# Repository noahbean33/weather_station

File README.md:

FPGA-Accelerated Digital Radio Receiver
A proof-of-concept digital radio that uses a Xilinx Artix-7 FPGA for real-time DSP and an ESP32 microcontroller for system control. The project demonstrates core competencies in FPGA design, embedded C, and RF system integration using off-the-shelf hardware modules.

This project is intentionally scoped for rapid development and focuses on creating a demonstrable system that showcases key engineering skills for a resume or portfolio.

Core Features
FPGA DSP: Real-time mono FM demodulation implemented in SystemVerilog.

MCU Control: An ESP32 running C (ESP-IDF) controls the radio tuner and user interface.

User Interface: A rotary encoder for tuning and an OLED screen to display the current frequency.

System Integration: All components are integrated on a breadboard or protoboard for straightforward assembly and debugging.

🛠️ Hardware Components
FPGA Board: Digilent Nexys A7 (or similar Artix-7 board).

Microcontroller: ESP32 Development Board (e.g., ESP32-DevKitC).

RF Tuner: Si4703 Breakout Board. This module simplifies the RF stage by handling tuning and providing a standard I2S digital audio output.

Display: I2C OLED Display (e.g., SSD1306 128x64).

Audio Output: I2S Amplifier Breakout Board (e.g., MAX98357A). This accepts the digital audio stream directly from the FPGA.

Input Control: One rotary encoder for tuning.

Power Supply: USB power or a benchtop power supply.

🏗️ System Architecture
Code snippet

graph TD
    A[Antenna] --> RF_TUNER;
    RF_TUNER[Si4703 Tuner Breakout];
    UI_Knob[Tuning Knob] --> ESP32;
    ESP32[ESP32 Dev Board (C Firmware)];
    ESP32 -- I2C --> RF_TUNER;
    ESP32 -- I2C --> OLED[OLED Display];

    subgraph "FPGA DSP (Artix-7)"
        ARTIX7[Xilinx Artix-7 FPGA]
        I2S_IN[I2S Input]
        FM_DEMOD[Mono FM Demodulator]
        I2S_OUT[I2S Output]

        I2S_IN --> FM_DEMOD;
        FM_DEMOD --> I2S_OUT;
    end

    RF_TUNER -- Digital Audio (I2S) --> I2S_IN;
    I2S_OUT --> DAC_AMP[I2S DAC/Amplifier];
    DAC_AMP --> Speaker;
System Flow:

The ESP32 instructs the Si4703 Tuner via I2C to tune to a specific frequency.

The tuner receives the radio signal and outputs a digital I2S audio stream.

The Artix-7 FPGA receives the I2S stream, performs mono FM demodulation in real-time, and outputs a processed I2S stream.

An I2S Amplifier receives the clean digital audio from the FPGA, converts it to analog, and drives a speaker.

The ESP32 displays the current frequency on the OLED screen.

💻 Software & Tools
FPGA Development:

Language: SystemVerilog

Toolchain: Xilinx Vivado Design Suite

Simulation: Vivado Simulator (XSIM)

Embedded Firmware (ESP32):

Language: C / C++

Framework: ESP-IDF (Espressif IoT Development Framework)

Tools: idf.py command-line tool

🚀 Project Plan
Phase 1: Core Controller Setup

[ ] Set up the ESP-IDF environment.

[ ] Interface the ESP32 with the OLED display and rotary encoder.

[ ] Write firmware to control the Si4703 tuner via I2C and display the frequency.

Milestone: Tune to an FM station and listen to the raw (undemodulated) output if possible, proving tuner control.

Phase 2: FPGA DSP Implementation

[ ] Set up the Xilinx Vivado environment.

[ ] Design and simulate a mono FM demodulator in SystemVerilog.

[ ] Implement I2S input and output interfaces on the FPGA.

[ ] Synthesize the design and program the Nexys A7 board.

Milestone: Pass a test I2S signal through the FPGA without modification (pass-through test).

Phase 3: System Integration & Testing

[ ] Connect all hardware modules on a breadboard.

[ ] Route the I2S signal from the tuner, through the FPGA, to the I2S amplifier.

[ ] Debug the complete system to achieve clear audio output.

Milestone: A fully functional radio that tunes via the knob and plays audio processed by the FPGA.

📁 Repository Structure
.
├── firmware/esp32             # ESP32 ESP-IDF C/C++ firmware
│   ├── main/
│   │   └── main.c
│   ├── components/
│   └── CMakeLists.txt
├── fpga/artix7                # Xilinx Artix-7 SystemVerilog code
│   ├── src/                   # Source files (.sv)
│   ├── sim/                   # Simulation files and testbenches
│   └── constraints/           # Pin and timing constraints (.xdc)
├── docs/                      # Documentation, diagrams, images
└── README.md
⚡ How to Build & Use
Firmware (ESP32)
Install the ESP-IDF toolchain from Espressif.

Navigate to firmware/esp32.

Build: idf.py build

Flash & Monitor: idf.py -p /dev/ttyUSB0 flash monitor (adjust port as needed).

FPGA (Artix-7)
Install the Xilinx Vivado Design Suite.

Open the Vivado project from the fpga/artix7 directory.

Run Synthesis, Implementation, and Generate Bitstream.

Program the FPGA using the Vivado Hardware Manager.

Acknowledgements
Digilent for the Nexys A7 board and support.

Espressif Systems for the ESP32 and the ESP-IDF.

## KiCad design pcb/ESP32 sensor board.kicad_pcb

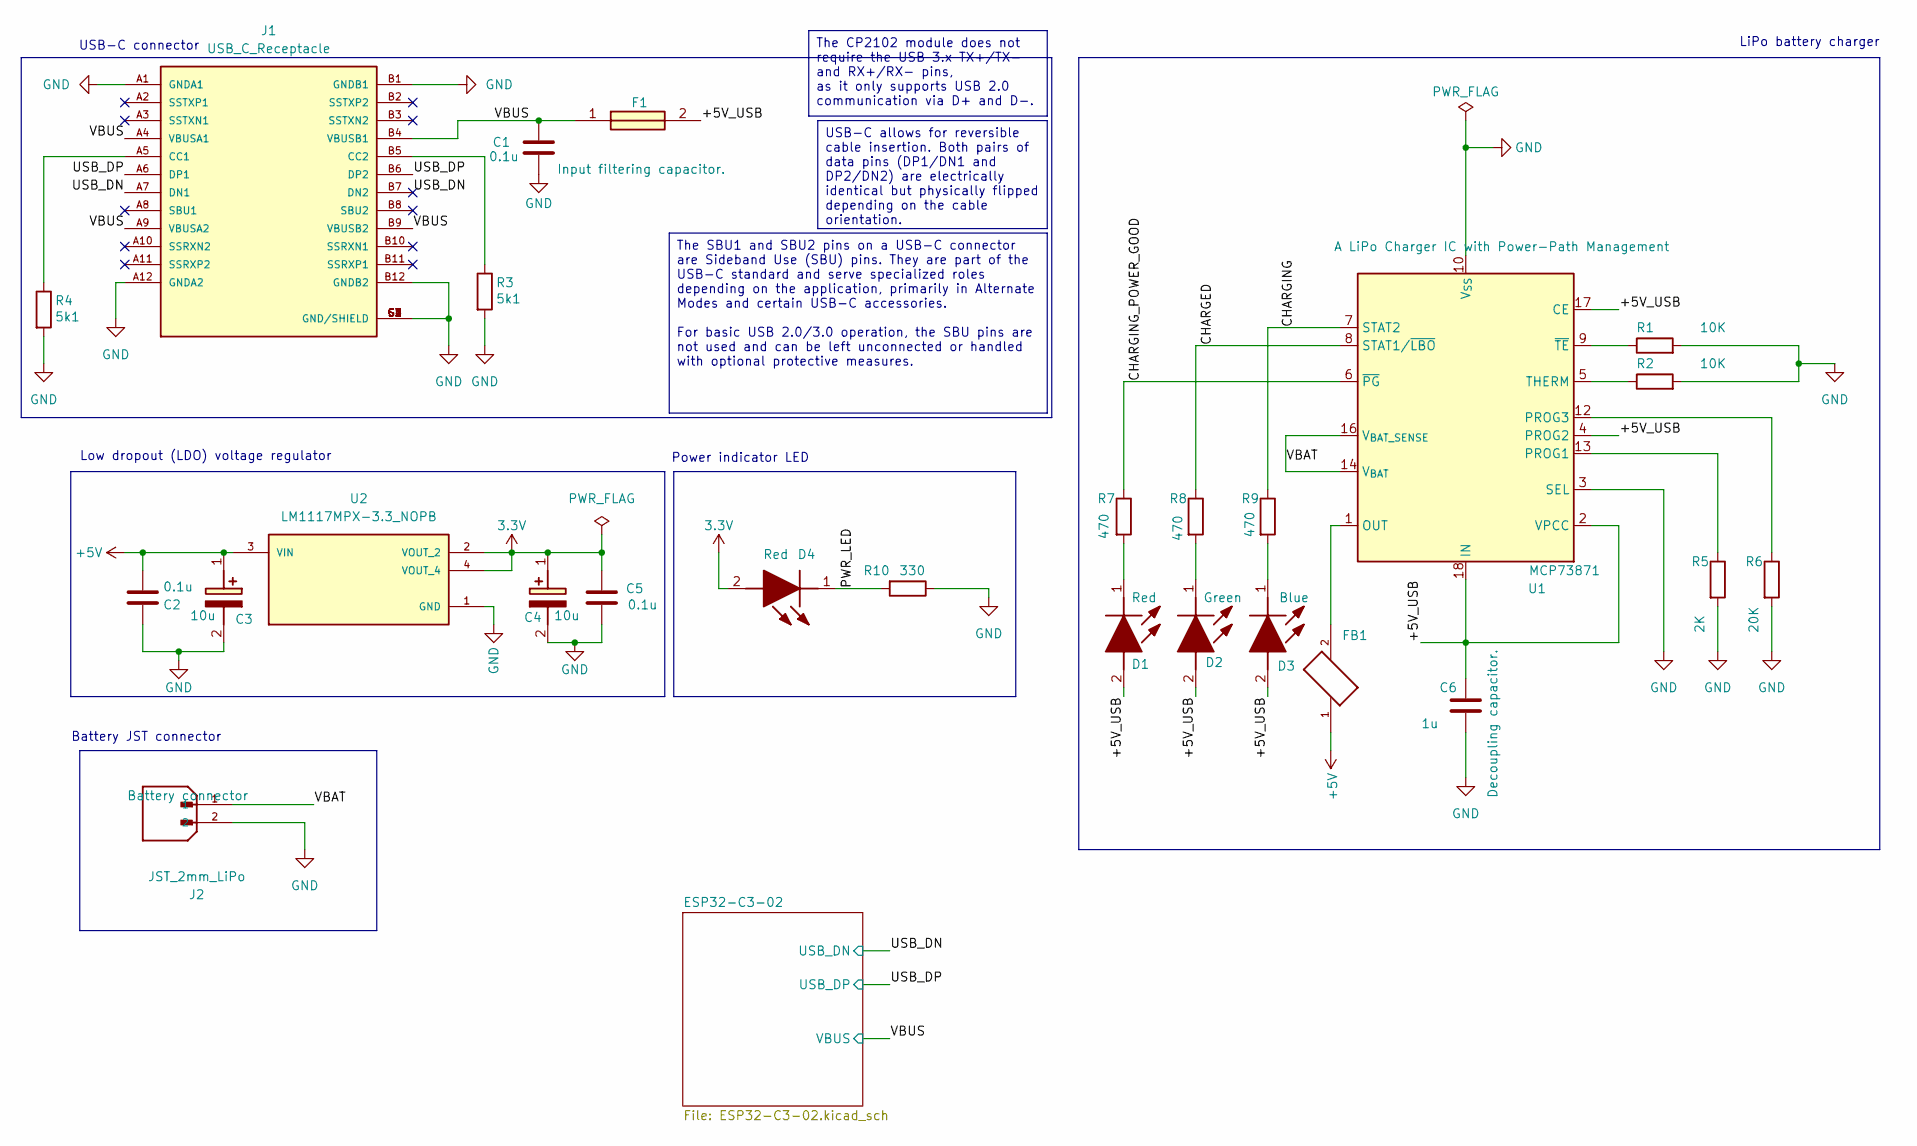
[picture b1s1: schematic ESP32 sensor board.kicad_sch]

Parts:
C1, C2, C5: 0.1u; C_0805_2012Metric; Voltage 1kV; Tolerance 100%
C3, C4: 10u; T491A; Voltage 1kV; Tolerance 100%; Manufacturer_Part_Number T491A106K010AT7280; Mouser Part Number 80-T491A106K107280
C6: 1u; C_0805_2012Metric; Voltage 1kV; Tolerance 100%
D1, D4: Red; LEDC2012X120N; Manufacturer_Part_Number LTST-C170KRKT; Mouser Part Number 859-LTST-C170KRKT
D2: Green; LEDC2012X120N; Manufacturer_Part_Number LTST-C170GKT; Mouser Part Number 859-LTST-C170GKT
D3: Blue; LEDC2012X120N; Manufacturer_Part_Number LTST-C170TBKT; Mouser Part Number 859-LTST-C170TBKT
F1: 0ZCH0110AF2E; FUSC3226X100N; Manufacturer_Part_Number 0ZCH0110AF2E
FB1: FBMJ2125HM330-T; BEADC2012X105N
J1: USB_C_Receptacle; BELFUSE_SS-52400-002; PARTREV A0
J2: JST_2mm_LiPo; JST_B2B-PH-SM4-TB; Manufacturer_Part_Number ?
R1, R2: 10K; R_0805_2012Metric
R3, R4: 5k1; R_0805_2012Metric
R5: 2K; R_0805_2012Metric
R6: 20K; R_0805_2012Metric
R7, R8, R9: 470; R_0805_2012Metric
R10: 330; R_0805_2012Metric
U1: MCP73871; QFN-20-1EP_4x4mm_P0.5mm_EP2.5x2.5mm; Manufacturer_Part_Number MCP73871-4CCI/ML
U2: LM1117MPX-3.3_NOPB; VREG_LM1117MPX-3.3; Mouser Part Number 926-LM1117MPX3.3NOPB

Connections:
3.3V: C4.1 (+), C5.1, D4.2 (A), U2.2 (VOUT_2), U2.4 (VOUT_4); also elsewhere on the board
+5V: C2.1, C3.1 (+), FB1.1, U2.3 (VIN)
/+5V_USB: C6.1, D1.2 (A), D2.2 (A), D3.2 (A), F1.2, U1.2 (VPCC), U1.4 (PROG2), U1.17 (CE), U1.18 (IN), U1.19 (IN)
/CHARGED: R8.1, U1.8 (STAT1/~LBO)
/CHARGING: R9.1, U1.7 (STAT2)
/CHARGING_POWER_GOOD: R7.1, U1.6 (~PG)
/PWR_LED: D4.1 (K), R10.2
/USB_DN: J1.A7 (DN1), J1.B7 (DN2); also elsewhere on the board
/USB_DP: J1.A6 (DP1), J1.B6 (DP2); also elsewhere on the board
/VBAT: J2.1, U1.14 (V_{BAT}), U1.15 (V_{BAT}), U1.16 (V_{BAT_SENSE})
/VBUS: C1.1, F1.1, J1.A4 (VBUSA1), J1.A9 (VBUSA2), J1.B4 (VBUSB1), J1.B9 (VBUSB2); also elsewhere on the board
GND: C1.2, C2.2, C3.2 (-), C4.2 (-), C5.2, C6.2, J1.A1 (GNDA1), J1.A12 (GNDA2), J1.B1 (GNDB1), J1.B12 (GNDB2), J1.G1 (GND/SHIELD), J1.G2 (GND/SHIELD), J1.G3 (GND/SHIELD), J1.G4 (GND/SHIELD), J1.S1 (GND/SHIELD), J1.S2 (GND/SHIELD), J1.S3 (GND/SHIELD), J1.S4 (GND/SHIELD), J2.2, R1.2, R2.2, R3.2, R4.2, R5.2, R6.2, R10.1, U1.3 (SEL), U1.10 (V_{SS}), U1.11 (V_{SS}), U1.21 (V_{SS}), U2.1 (GND); also elsewhere on the board
unnamed: D1.1 (K), R7.2
unnamed: D2.1 (K), R8.2
unnamed: D3.1 (K), R9.2
unnamed: FB1.2, U1.1 (OUT), U1.20 (OUT)
unnamed: J1.A5 (CC1), R4.1
unnamed: J1.B5 (CC2), R3.1
unnamed: R5.1, U1.13 (PROG1)
unnamed: R6.1, U1.12 (PROG3)
unnamed: R2.1, U1.5 (THERM)
unnamed: R1.1, U1.9 (~TE)

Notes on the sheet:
USB-C connector
LiPo battery charger
Power indicator LED
Low dropout (LDO) voltage regulator
Battery JST connector
The CP2102 module does not require the USB 3.x TX+/TX- and RX+/RX- pins, as it only supports USB 2.0 communication via D+ and D-.
The SBU1 and SBU2 pins on a USB-C connector are Sideband Use (SBU) pins. They are part of the USB-C standard and serve specialized roles depending on the application, primarily in Alternate Modes and certain USB-C accessories. For basic USB 2.0/3.0 operation, the SBU pins are not used and can be le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
USB-C allows for reversible cable insertion. Both pairs of data pins (DP1/DN1 and DP2/DN2) are electrically identical but physically flipped depending on the cable orientation.

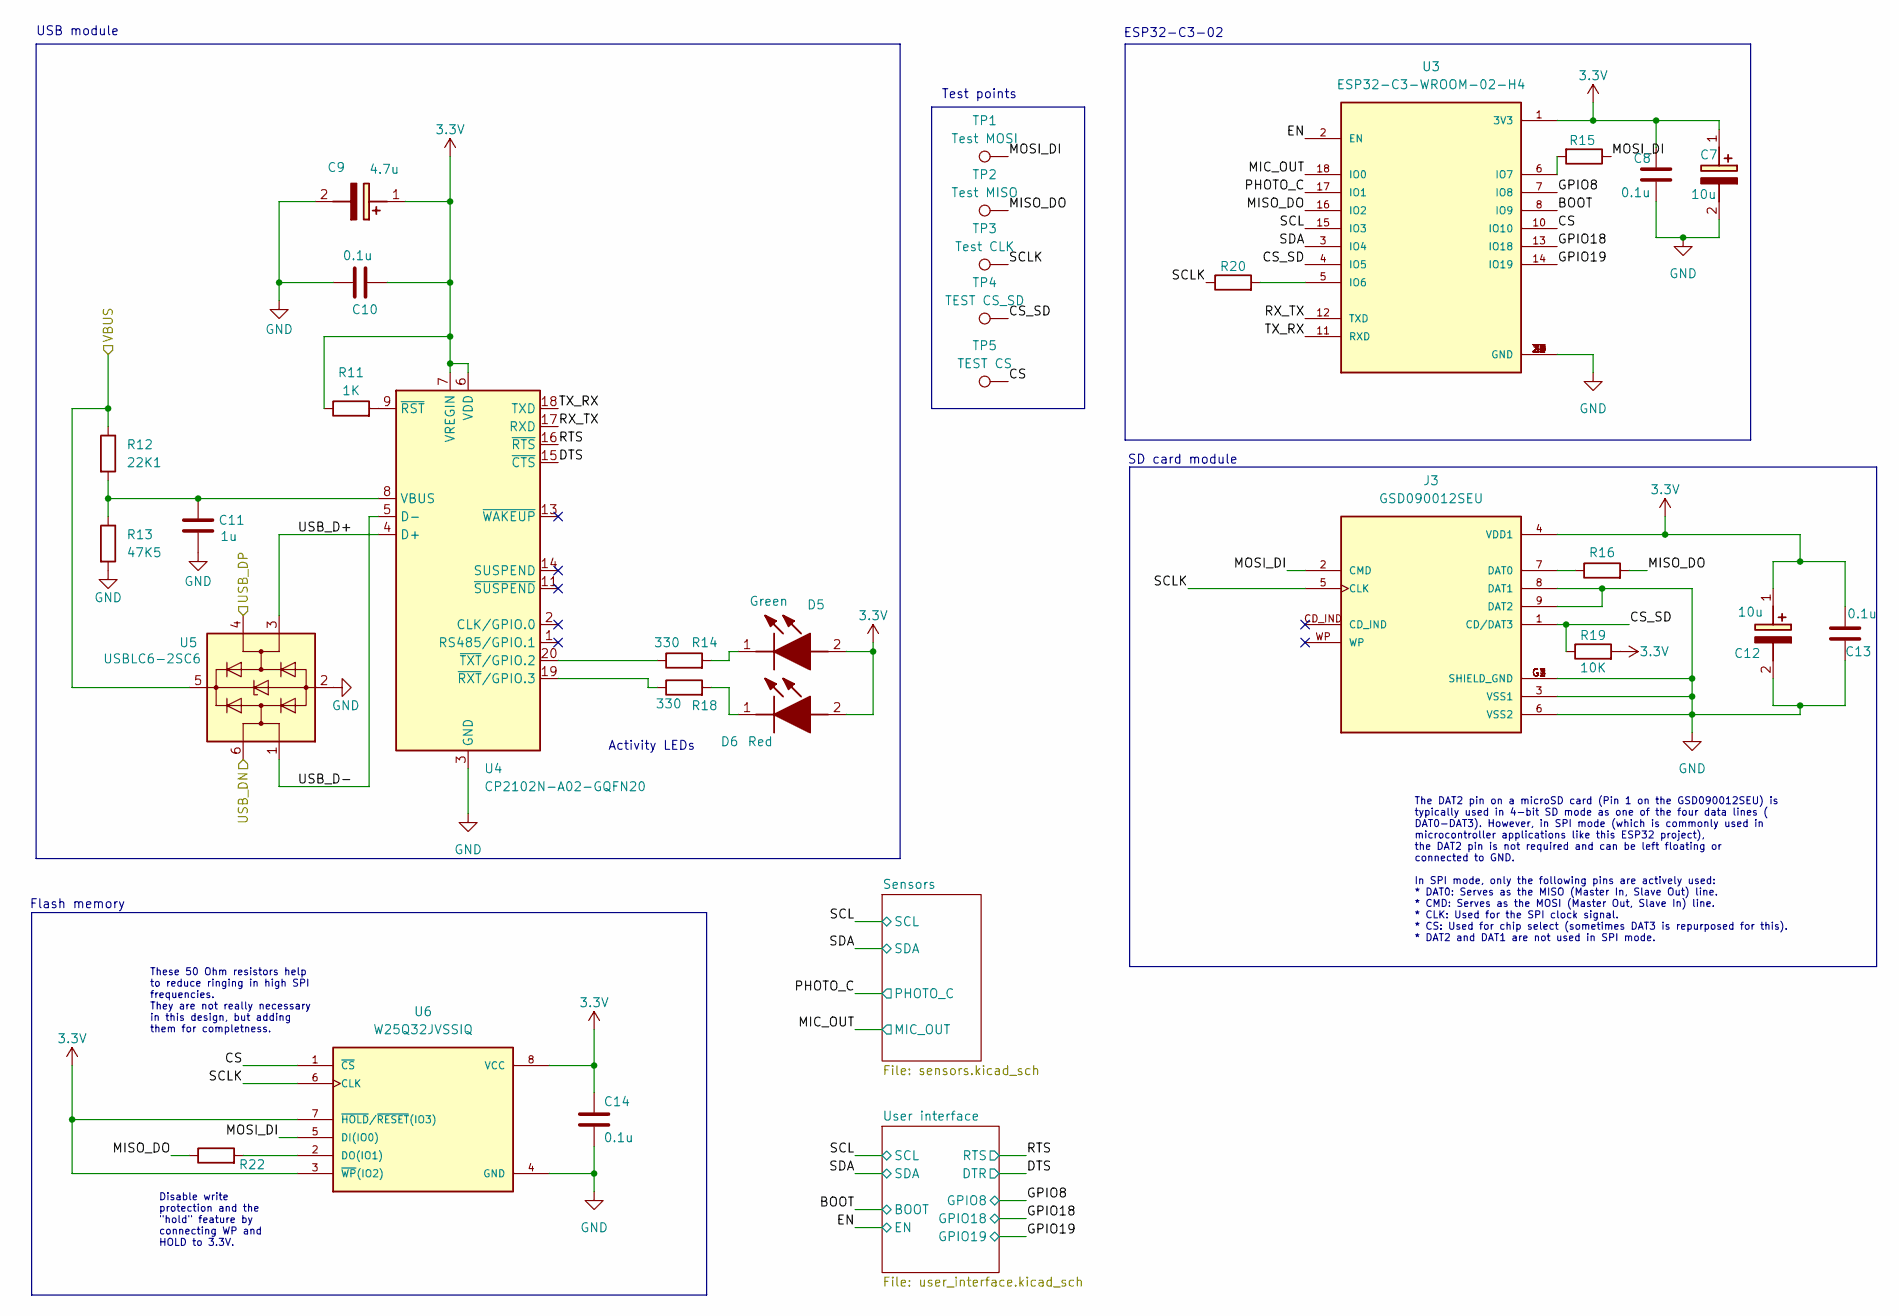
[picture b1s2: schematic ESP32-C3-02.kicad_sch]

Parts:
C7, C12: 10u; T491A; Voltage 1kV; Tolerance 100%; Manufacturer_Part_Number T491A106K010AT7280; Mouser Part Number 80-T491A106K107280
C8, C10, C13, C14: 0.1u; C_0805_2012Metric; Voltage 1kV; Tolerance 100%
C9: 4.7u; T491A; Voltage 1kV; Tolerance 100%; Manufacturer_Part_Number T491A106K010AT7280; Mouser Part Number 80-T491A106K107280
C11: 1u; C_0805_2012Metric; Voltage 1kV; Tolerance 100%
D5: Green; LEDC2012X120N; Manufacturer_Part_Number LTST-C170GKT; Mouser Part Number 859-LTST-C170GKT
D6: Red; LEDC2012X120N; Manufacturer_Part_Number LTST-C170KRKT; Mouser Part Number 859-LTST-C170KRKT
J3: GSD090012SEU; AMPHENOL_GSD090012SEU; PARTREV E
R11: 1K; R_0805_2012Metric
R12: 22K1; R_0805_2012Metric
R13: 47K5; R_0805_2012Metric
R14, R18: 330; R_0805_2012Metric
R15, R16, R20, R22: 50; R_0805_2012Metric
R19: 10K; R_0805_2012Metric
TP1: Test MOSI; TestPoint_Pad_D1.0mm
TP2: Test MISO; TestPoint_Pad_D1.0mm
TP3: Test CLK; TestPoint_Pad_D1.0mm
TP4: TEST CS_SD; TestPoint_Pad_D1.0mm
TP5: TEST CS; TestPoint_Pad_D1.0mm
U3: ESP32-C3-WROOM-02-H4; MODULE_ESP32-C3-WROOM-02-H4; Manufacturer_Part_Number ESP32-C3-WROOM-02-H4
U4: CP2102N-A02-GQFN20; SiliconLabs_QFN-20-1EP_3x3mm_P0.5mm_EP1.8x1.8mm; Manufacturer_Part_Number CP2102N-A02-GQFN20
U5: USBLC6-2SC6; SOT-23-6; Manufacturer_Part_Number USBLC6-2SC6; Mouser Part Number 511-USBLC6-2SC6
U6: W25Q32JVSSIQ; SOIC127P790X216-8N; M_PART_NUMBER W25QXX

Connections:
3.3V: C7.1 (+), C8.1, C9.1 (+), C10.1, C12.1 (+), C13.2, C14.1, D5.2 (A), D6.2 (A), J3.4 (VDD1), R11.1, R19.2, U3.1 (3V3), U4.6 (VDD), U4.7 (VREGIN), U6.3 (~WP(IO2)), U6.7 (~HOLD/~RESET(IO3)), U6.8 (VCC); also elsewhere on the board
/ESP32-C3-02/BOOT: U3.8 (IO9); also elsewhere on the board
/ESP32-C3-02/CS: TP5.1 (1_1), U3.10 (IO10), U6.1 (~CS)
/ESP32-C3-02/CS_SD: J3.1 (CD/DAT3), R19.1, TP4.1 (1_1), U3.4 (IO5)
/ESP32-C3-02/DTS: U4.15 (~CTS); also elsewhere on the board
/ESP32-C3-02/EN: U3.2 (EN); also elsewhere on the board
/ESP32-C3-02/GPIO8: U3.7 (IO8); also elsewhere on the board
/ESP32-C3-02/GPIO18: U3.13 (IO18); also elsewhere on the board
/ESP32-C3-02/GPIO19: U3.14 (IO19); also elsewhere on the board
/ESP32-C3-02/MIC_OUT: U3.18 (IO0); also elsewhere on the board
/ESP32-C3-02/MISO_DO: R16.2, R22.1, TP2.1 (1_1), U3.16 (IO2)
/ESP32-C3-02/MOSI_DI: J3.2 (CMD), R15.1, TP1.1 (1_1), U6.5 (DI(IO0))
/ESP32-C3-02/PHOTO_C: U3.17 (IO1); also elsewhere on the board
/ESP32-C3-02/RTS: U4.16 (~RTS); also elsewhere on the board
/ESP32-C3-02/RX_TX: U3.12 (TXD), U4.17 (RXD)
/ESP32-C3-02/SCL: U3.15 (IO3); also elsewhere on the board
/ESP32-C3-02/SCLK: J3.5 (CLK), R20.1, TP3.1 (1_1), U6.6 (CLK)
/ESP32-C3-02/SDA: U3.3 (IO4); also elsewhere on the board
/ESP32-C3-02/TX_RX: U3.11 (RXD), U4.18 (TXD)
/ESP32-C3-02/USB_D+: U4.4 (D+), U5.3 (I/O2)
/ESP32-C3-02/USB_D-: U4.5 (D-), U5.1 (I/O1)
/USB_DN: U5.6 (I/O1); also elsewhere on the board
/USB_DP: U5.4 (I/O2); also elsewhere on the board
/VBUS: R12.1, U5.5 (VBUS); also elsewhere on the board
GND: C7.2 (-), C8.2, C9.2 (-), C10.2, C11.2, C12.2 (-), C13.1, C14.2, J3.3 (VSS1), J3.6 (VSS2), J3.8 (DAT1), J3.9 (DAT2), J3.G1 (SHIELD_GND), J3.G2 (SHIELD_GND), J3.G3 (SHIELD_GND), J3.G4 (SHIELD_GND), R13.2, U3.9 (GND), U3.19 (GND), U3.20 (GND), U3.21 (GND), U3.22 (GND), U3.23 (GND), U3.24 (GND), U3.25 (GND), U3.26 (GND), U3.27 (GND), U3.28 (GND), U3.29 (GND), U3.30 (GND), U3.31 (GND), U3.32 (GND), U3.33 (GND), U3.34 (GND), U3.35 (GND), U3.36 (GND), U3.37 (GND), U3.38 (GND), U3.39 (GND), U4.3 (GND), U4.12 (GND), U4.21 (GND), U5.2 (GND), U6.4 (GND); also elsewhere on the board
unnamed: D5.1 (K), R14.2
unnamed: D6.1 (K), R18.2
unnamed: J3.7 (DAT0), R16.1
unnamed: R20.2, U3.5 (IO6)
unnamed: R15.2, U3.6 (IO7)
unnamed: C11.1, R12.2, R13.1, U4.8 (VBUS)
unnamed: R11.2, U4.9 (~RST)
unnamed: R18.1, U4.19 (~RXT/GPIO.3)
unnamed: R14.1, U4.20 (~TXT/GPIO.2)
unnamed: R22.2, U6.2 (DO(IO1))

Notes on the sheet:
SD card module
Activity LEDs
Flash memory
USB module
Test points
ESP32-C3-02
Disable write protection and the "hold" feature by connecting WP and HOLD to 3.3V.
The DAT2 pin on a microSD card (Pin 1 on the GSD090012SEU) is typically used in 4-bit SD mode as one of the four data lines ( DAT0-DAT3). However, in SPI mode (which is commonly used in microcontroller applications like this ESP32 project), the DAT2 pin is not required and can be left floating or c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
These 50 Ohm resistors help to reduce ringing in high SPI frequencies. They are not really necessary in this design, but adding them for completness.

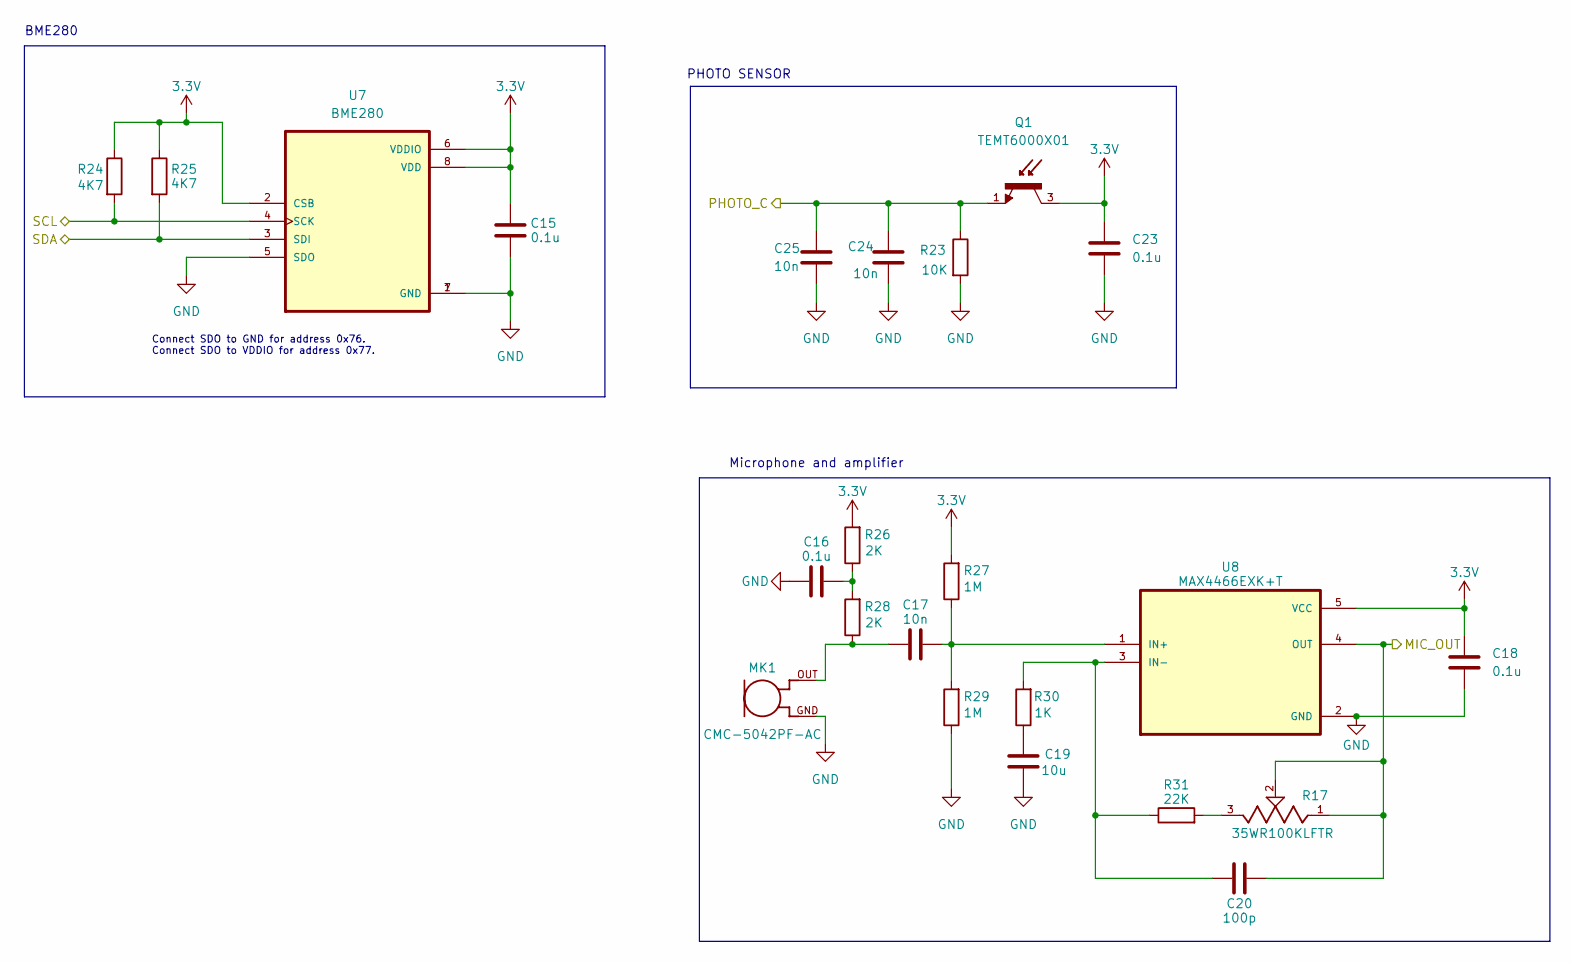
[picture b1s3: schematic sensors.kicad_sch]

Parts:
C15: 0.1u; C_0805_2012Metric; Voltage 1kV; Tolerance 100%
C16, C18, C23: 0.1u; C_0805_2012Metric
C17, C24, C25: 10n; C_0805_2012Metric
C19: 10u; C_0805_2012Metric
C20: 100p; C_0805_2012Metric
MK1: CMC-5042PF-AC; CUI_CMC-5042PF-AC; Manufacturer_Part_Number CMC-5042PF-AC
Q1: TEMT6000X01; TRANS_TEMT6000X01; PARTREV 1.9
R17: 35WR100KLFTR; TRIM_35WR100KLFTR; PARTREV D
R23: 10K; R_0805_2012Metric
R24, R25: 4K7; R_0805_2012Metric
R26, R28: 2K; R_0805_2012Metric
R27, R29: 1M; R_0805_2012Metric
R30: 1K; R_0805_2012Metric
R31: 22K; R_0805_2012Metric
U7: BME280; PSON65P250X250X100-8N; Manufacturer_Part_Number BME280
U8: MAX4466EXK+T; SOT65P210X110-5N; Manufacturer_Part_Number MAX4466EXK+T

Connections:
3.3V: C15.2, C18.1, C23.1, Q1.3, R24.1, R25.1, R26.2, R27.2, U7.2 (CSB), U7.6 (VDDIO), U7.8 (VDD), U8.5 (VCC); also elsewhere on the board
/ESP32-C3-02/MIC_OUT: C20.2, R17.1, R17.2, U8.4 (OUT); also elsewhere on the board
/ESP32-C3-02/PHOTO_C: C24.1, C25.1, Q1.1, R23.1; also elsewhere on the board
/ESP32-C3-02/SCL: R24.2, U7.4 (SCK); also elsewhere on the board
/ESP32-C3-02/SDA: R25.2, U7.3 (SDI); also elsewhere on the board
GND: C15.1, C16.2, C18.2, C19.1, C23.2, C24.2, C25.2, MK1.GND, R23.2, R29.1, U7.1 (GND), U7.5 (SDO), U7.7 (GND), U8.2 (GND); also elsewhere on the board
unnamed: C16.1, R26.1, R28.2
unnamed: C17.2, MK1.OUT, R28.1
unnamed: C19.2, R30.1
unnamed: R17.3, R31.2
unnamed: C17.1, R27.1, R29.2, U8.1 (IN+)
unnamed: C20.1, R30.2, R31.1, U8.3 (IN-)

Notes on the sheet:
PHOTO SENSOR
Microphone and amplifier
BME280
Connect SDO to GND for address 0x76. Connect SDO to VDDIO for address 0x77.

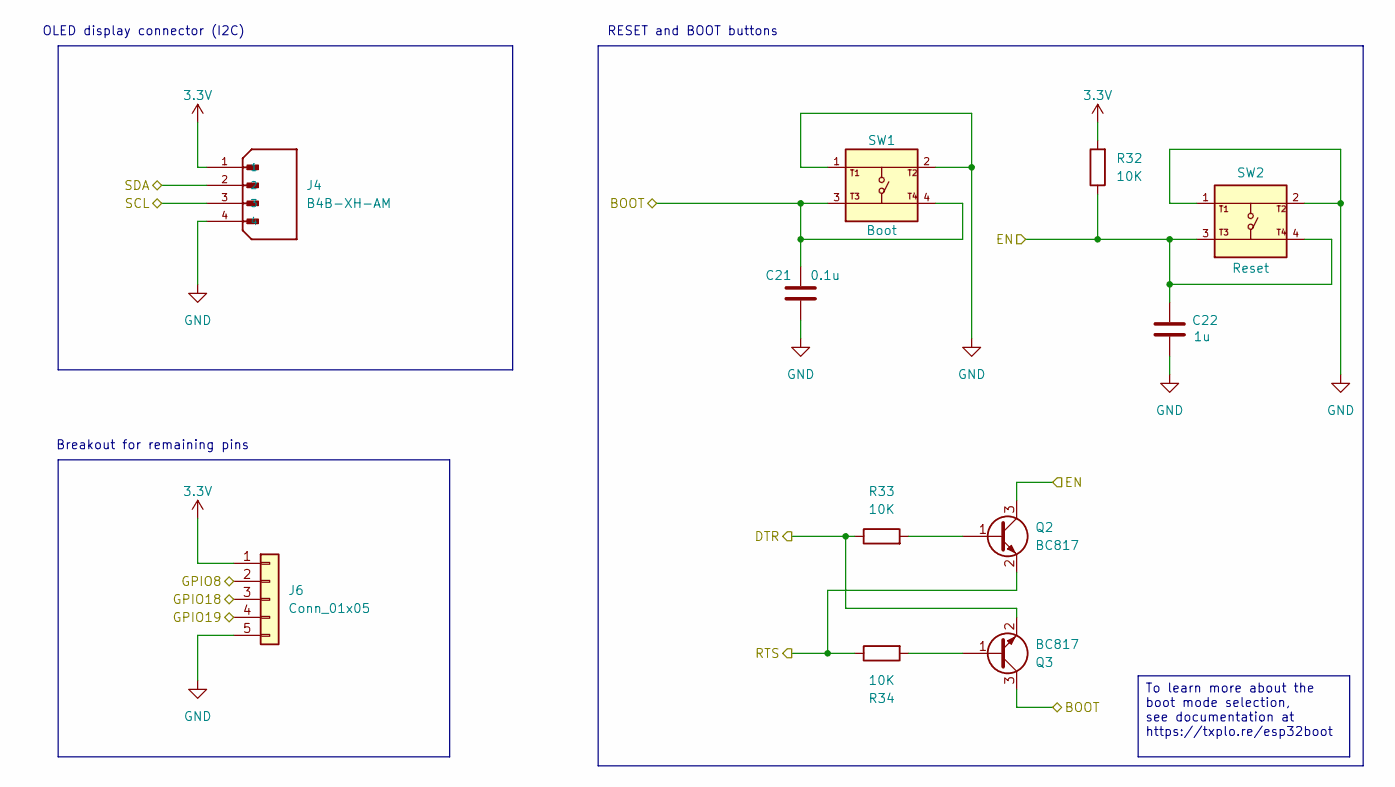
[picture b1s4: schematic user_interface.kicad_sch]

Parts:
C21: 0.1u; C_0805_2012Metric; Voltage 1kV; Tolerance 100%
C22: 1u; C_0805_2012Metric; Voltage 1kV; Tolerance 100%
J4: B4B-XH-AM; JST_B4B-XH-AM__LF__SN_; PARTREV N/A
J6: Conn_01x05; PinHeader_1x05_P2.54mm_Vertical
Q2, Q3: BC817; SOT-23; Manufacturer_Part_Number BC817
R32, R33, R34: 10K; R_0805_2012Metric
SW1, SW2: 1101NE; SW_USLPT2819DT2TR; Mfg Part# 8-004 SMD Button 8x3.6mm Height=2.5mm

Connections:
3.3V: J4.1, J6.1, R32.2; also elsewhere on the board
/ESP32-C3-02/BOOT: C21.1, Q3.3 (C), SW1.3, SW1.4; also elsewhere on the board
/ESP32-C3-02/DTS: Q3.2 (E), R33.1; also elsewhere on the board
/ESP32-C3-02/EN: C22.1, Q2.3 (C), R32.1, SW2.3, SW2.4; also elsewhere on the board
/ESP32-C3-02/GPIO8: J6.2; also elsewhere on the board
/ESP32-C3-02/GPIO18: J6.3; also elsewhere on the board
/ESP32-C3-02/GPIO19: J6.4; also elsewhere on the board
/ESP32-C3-02/RTS: Q2.2 (E), R34.1; also elsewhere on the board
/ESP32-C3-02/SCL: J4.3; also elsewhere on the board
/ESP32-C3-02/SDA: J4.2; also elsewhere on the board
GND: C21.2, C22.2, J4.4, J6.5, SW1.1, SW1.2, SW2.1, SW2.2; also elsewhere on the board
unnamed: Q2.1 (B), R33.2
unnamed: Q3.1 (B), R34.2

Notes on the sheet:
OLED display connector (I2C)
RESET and BOOT buttons
Breakout for remaining pins
To learn more about the boot mode selection, see documentation at https://txplo.re/esp32boot

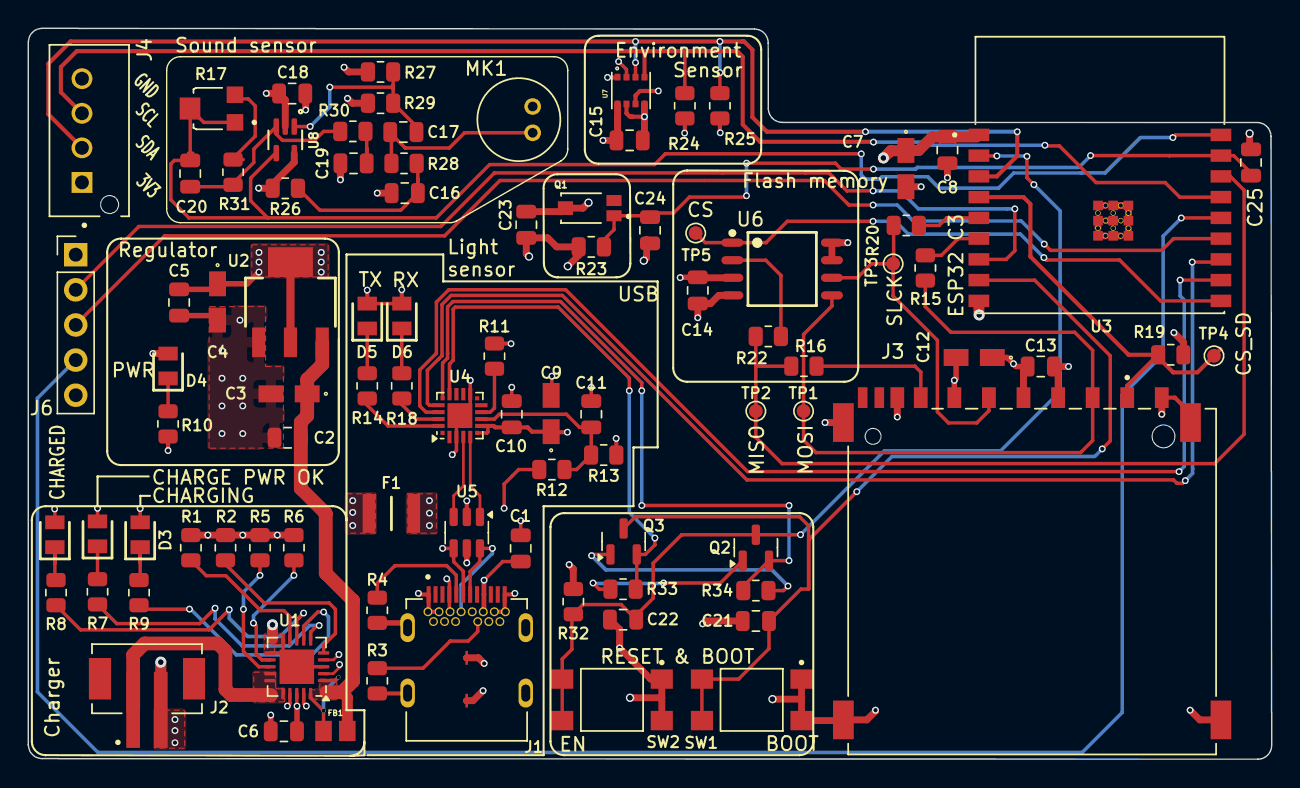
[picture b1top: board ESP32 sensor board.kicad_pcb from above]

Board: 4 copper layers, 89.9 x 52.8 mm, 90 parts (0 on the bottom side), 60 nets.

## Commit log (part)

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2025-07-06 Update README.md
    updated readme
2025-10-07 set up project
2025-10-23 added images
2026-01-25 added license and references
2026-01-27 moved images into separate folder
2026-05-03 added content
2026-05-17 organized repo
2026-06-03 added code comments
